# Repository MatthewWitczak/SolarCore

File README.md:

## Project description
SolarCore is a compact, high-efficiency DC/DC buck converter designed to operate from a 12 V solar panel deliver a 3.3 V output for embedded electronics.
The converter is based on the Texas Instruments LMR33630 and integrates measurement circuits allowing a STM32L432KC microcontroller to monitor both input and output voltage in real time.

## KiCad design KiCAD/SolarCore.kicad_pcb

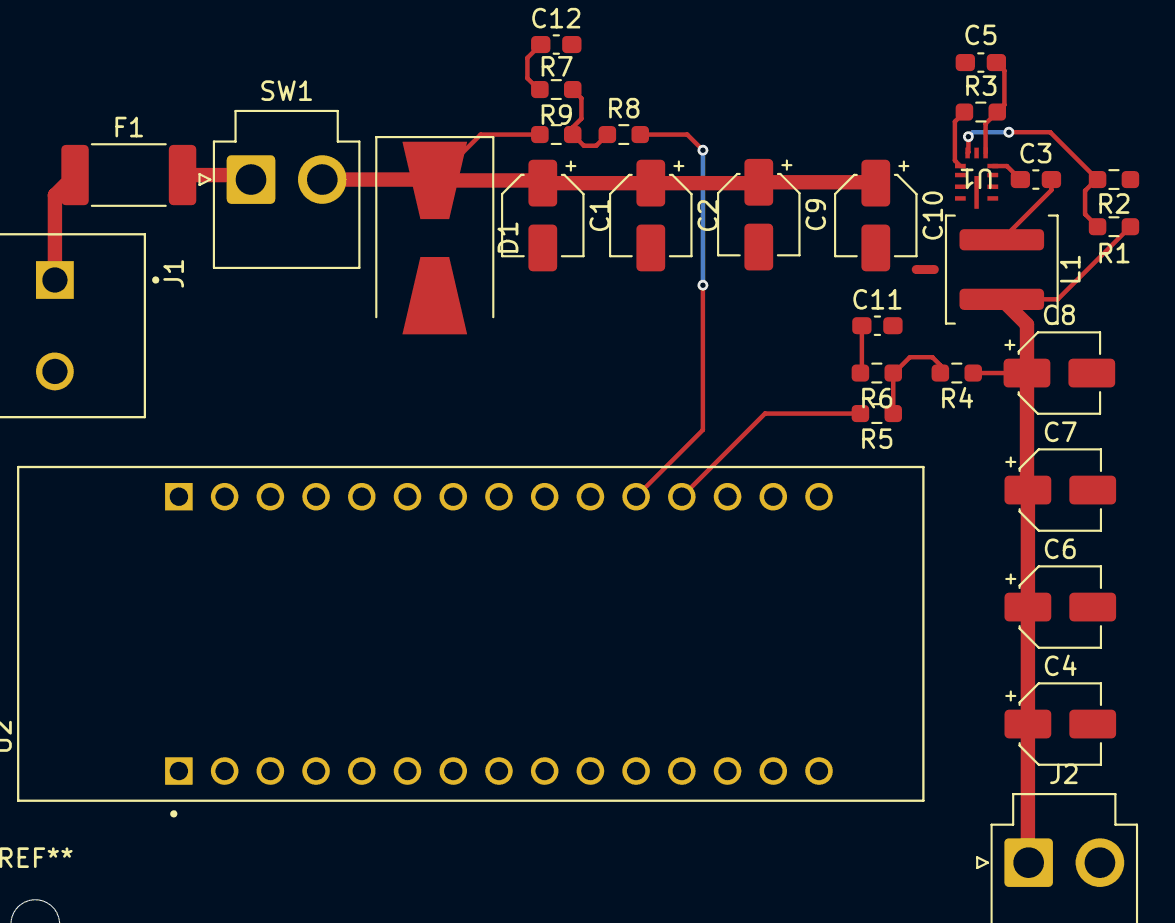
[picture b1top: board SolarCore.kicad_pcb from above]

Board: 4 copper layers, 30 parts (0 on the bottom side), 17 nets.

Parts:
C1, C2: 4.7u; CP_Elec_4x5.4
C3: 0.1u; C_0603_1608Metric_Pad1.08x0.95mm_HandSolder
C4, C6, C7, C8: 22u; CP_Elec_4x5.4
C5: 1u; C_0603_1608Metric_Pad1.08x0.95mm_HandSolder
C9, C10: 100n; CP_Elec_4x5.4
C11, C12: 2.2n; C_0603_1608Metric_Pad1.08x0.95mm_HandSolder
D1: D_Zener; D_SMB-SMC_Universal_Handsoldering
F1: Fuse; Fuse_2512_6332Metric_Pad1.52x3.35mm_HandSolder
J1: Conn_01x02_MountingPin; TE_282857-2
J2: Conn_01x02_MountingPin; JST_VH_B2P-VH_1x02_P3.96mm_Vertical
L1: 6.8u; L_Coilcraft_XAL5030-XXX
NT1: NetTie_2; NetTie-2_SMD_Pad0.5mm
R1, R3, R4, R5, R6: 100k; R_0603_1608Metric_Pad0.98x0.95mm_HandSolder
R2: 43.3k; R_0603_1608Metric_Pad0.98x0.95mm_HandSolder
R7: 75k; R_0603_1608Metric_Pad0.98x0.95mm_HandSolder
R8: 27k; R_0603_1608Metric_Pad0.98x0.95mm_HandSolder
R9: 33k; R_0603_1608Metric_Pad0.98x0.95mm_HandSolder
SW1: SW_SPST; JST_VH_B2P-VH_1x02_P3.96mm_Vertical
U1: LMR33630ARNXR; RNX0012B
U2: NUCLEO-L432KC; MODULE_NUCLEO-L432KC

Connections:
AGND: C5.2, C11.2, C12.2, NT1.2, U1.3 (NC), U1.6 (AGND), U1.11 (PGND), U2.CN3_4 (GND_CN3), U2.CN4_2 (GND_CN4)
unnamed: C11.1, R6.2
unnamed: C12.1, R9.2
unnamed: F1.1, J1.1
unnamed: R4.2, R5.1, R6.1
unnamed: R7.2, R8.1, R9.1
unnamed: F1.2, SW1.1 (A)
unnamed: C3.1, U1.4 (BST)
unnamed: R1.2, R2.1, U1.7 (FB)
unnamed: C3.2, L1.1, U1.12 (SW)
unnamed: C5.1, R3.2, U1.5 (VCC)
PA0: R5.2, U2.CN4_12 (PA0)
PA1: R8.2, U2.CN4_11 (PA1)
PG: R3.1, U1.8 (PG)
PGND: C1.2, C2.2, C4.2, C6.2, C7.2, C8.2, C9.2, C10.2, D1.2 (A), J1.2, J2.2, NT1.1, R2.2, U1.1 (PGND)
V_IN_MEAS: C1.1, C2.1, C9.1, C10.1, D1.1 (K), R7.1, SW1.2 (B), U1.9 (EN), U1.10 (VIN)
V_OUT_MEAS: C4.1, C6.1, C7.1, C8.1, J2.1, L1.2, R1.1, R4.1

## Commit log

2025-11-09 Upload gitignore
2025-11-09 .gitignore update
2025-11-09 Update .gitignore and refresh tracked files
2025-11-09 Schematic update V1
2025-11-10 Schematic update V2
2025-11-10 IC model update
2025-11-10 Reorganizing the workspace
2025-11-10 Add voltage measure
2025-11-10 Project reorganization
2025-11-10 Input voltage measure
2025-11-10 Add footprints
2025-11-10 Increasing circuit safety
2025-11-10 First version of the schematic
2025-11-11 Final schematic V1
2025-11-11 Final schematic V2
2025-11-11 Final schematic V3
2025-11-11 Visual corrections to the schematic
2025-11-12 Final schematic V4
2025-11-12 Final schematic V5
2025-11-13 PCB V1
2025-11-14 PCB V2
2025-11-14 PCB V3
2025-11-15 PCB V4
